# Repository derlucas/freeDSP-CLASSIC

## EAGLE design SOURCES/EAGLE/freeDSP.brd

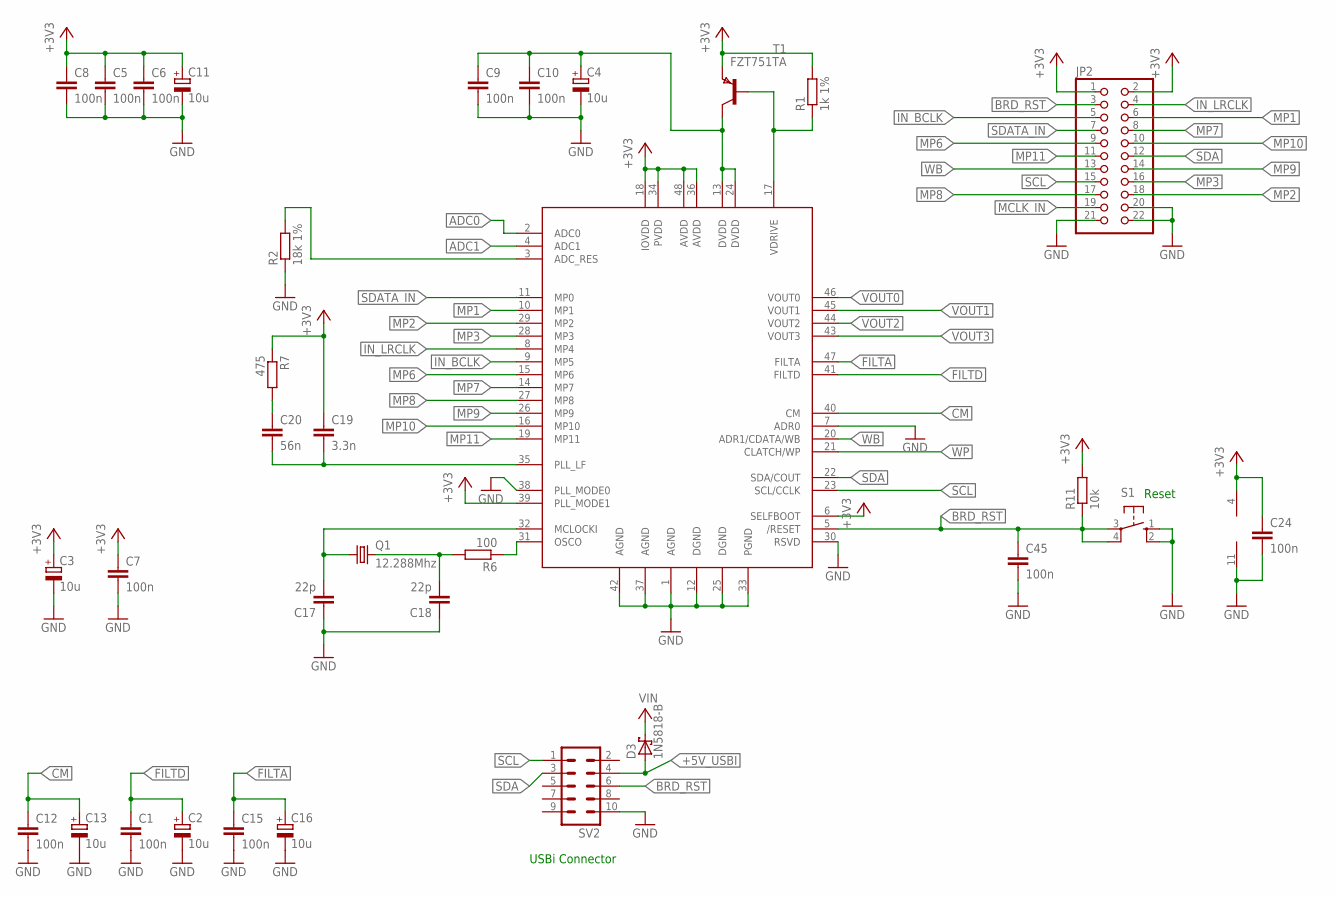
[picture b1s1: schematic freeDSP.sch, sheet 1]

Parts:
C1, C5, C6, C7, C8, C9, C10, C12, C15, C24, C45: 100n; C025-025X050
C2, C3, C4, C11, C13, C16: 10u; E1,8-4
C17, C18: 22p; C025-025X050
C19: 3.3n; C025-025X050
C20: 56n; C025-025X050
D3: 1N5818-B; DO41-7.6
IC3: AD8608R; SO-14
JP2: PINHD-2X11; 2X11
Q1: 12.288Mhz; HC49/S
R1: 1k 1%; 0207/10
R2: 18k 1%; 0207/10
R6: 100; 0207/10
R7: 475; 0207/10
R11: 10k; 0207/10
S1: 10-XX; B3F-10XX
SV2: ML10
T1: FZT751TA; SOT223
U$1: ADAU1701; LQFP-48

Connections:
1V8: C4.+, C9.1, C10.1, T1.2 (C), T1.4 (C), U$1.13 (DVDD), U$1.24 (DVDD)
+3V3: C3.+, C5.1, C6.1, C7.1, C8.1, C11.+, C19.1, C24.1, IC3.4 (V+), JP2.1, JP2.2, R1.2, R7.1, R11.2, T1.3 (E), U$1.6 (SELFBOOT), U$1.18 (IOVDD), U$1.34 (PVDD), U$1.36 (AVDD), U$1.39 (PLL_MODE1), U$1.48 (AVDD); also elsewhere on the board
+5V_USBI: D3.A, SV2.4
ADC0: U$1.2 (ADC0); also elsewhere on the board
ADC1: U$1.4 (ADC1); also elsewhere on the board
BRD_RST: C45.1, JP2.3, R11.1, S1.3, S1.4 (P1), SV2.6, U$1.5 (/RESET); also elsewhere on the board
CM: C12.1, C13.+, U$1.40 (CM)
FILTA: C15.1, C16.+, U$1.47 (FILTA)
FILTD: C1.1, C2.+, U$1.41 (FILTD)
GND: C1.2, C2.-, C3.-, C4.-, C5.2, C6.2, C7.2, C8.2, C9.2, C10.2, C11.-, C12.2, C13.-, C15.2, C16.-, C17.1, C18.1, C24.2, C45.2, IC3.11 (V-), JP2.20, JP2.21, JP2.22, R2.1, S1.1 (S), S1.2 (S1), SV2.10, U$1.1 (AGND), U$1.7 (ADR0), U$1.12 (DGND), U$1.25 (DGND), U$1.30 (RSVD), U$1.33 (PGND), U$1.37 (AGND), U$1.38 (PLL_MODE0), U$1.42 (AGND); also elsewhere on the board
IN_BCLK: JP2.5, U$1.9 (MP5)
IN_LRCLK: JP2.4, U$1.8 (MP4)
MCLK_IN: JP2.19
MP1: JP2.6, U$1.10 (MP1)
MP2: JP2.18, U$1.29 (MP2)
MP3: JP2.16, U$1.28 (MP3)
MP6: JP2.9, U$1.15 (MP6)
MP7: JP2.8, U$1.14 (MP7)
MP8: JP2.17, U$1.27 (MP8)
MP9: JP2.14, U$1.26 (MP9)
MP10: JP2.10, U$1.16 (MP10)
MP11: JP2.11, U$1.19 (MP11)
unnamed: R2.2, U$1.3 (ADC_RES)
unnamed: R1.1, T1.1 (B), U$1.17 (VDRIVE)
unnamed: C19.2, C20.2, U$1.35 (PLL_LF)
unnamed: C20.1, R7.2
unnamed: C18.2, Q1.2, R6.2
unnamed: R6.1, U$1.31 (OSCO)
unnamed: C17.2, Q1.1, U$1.32 (MCLOCKI)
SCL: JP2.15, SV2.1, U$1.23 (SCL/CCLK); also elsewhere on the board
SDA: JP2.12, SV2.3, U$1.22 (SDA/COUT); also elsewhere on the board
SDATA_IN: JP2.7, U$1.11 (MP0)
V+: D3.C; also elsewhere on the board
VOUT0: U$1.46 (VOUT0); also elsewhere on the board
VOUT1: U$1.45 (VOUT1); also elsewhere on the board
VOUT2: U$1.44 (VOUT2); also elsewhere on the board
VOUT3: U$1.43 (VOUT3); also elsewhere on the board
WB: JP2.13, U$1.20 (ADR1/CDATA/WB)
WP: U$1.21 (CLATCH/WP); also elsewhere on the board

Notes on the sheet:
Reset
USBi Connector

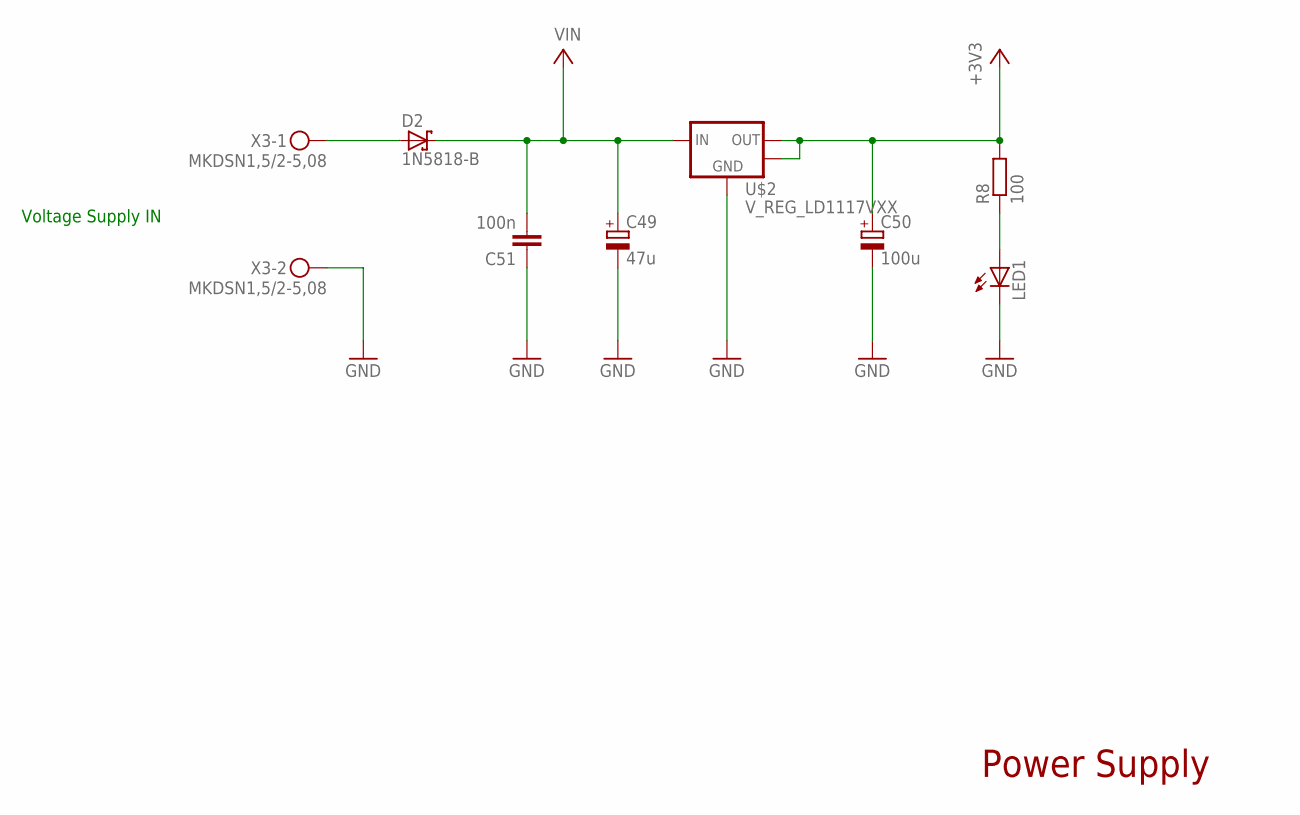
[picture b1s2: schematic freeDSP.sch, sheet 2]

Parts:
C49: 47u; E2,5-6
C50: 100u; E2,5-6
C51: 100n; C025-025X050
D2: 1N5818-B; DO41-7.6
LED1: LED3MM
R8: 100; 0207/10
U$2: V_REG_LD1117VXX; 78XXL
X3: MKDSN1,5/2-5,08

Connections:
+3V3: C50.+, R8.2, U$2.GND (OUT), U$2.OUT2; also elsewhere on the board
GND: C49.-, C50.-, C51.1, LED1.K (C), U$2.IN (GND), X3.2; also elsewhere on the board
unnamed: LED1.A, R8.1
unnamed: D2.A, X3.1
V+: C49.+, C51.2, D2.C, U$2.OUT (IN); also elsewhere on the board

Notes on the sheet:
Voltage Supply IN
Power Supply

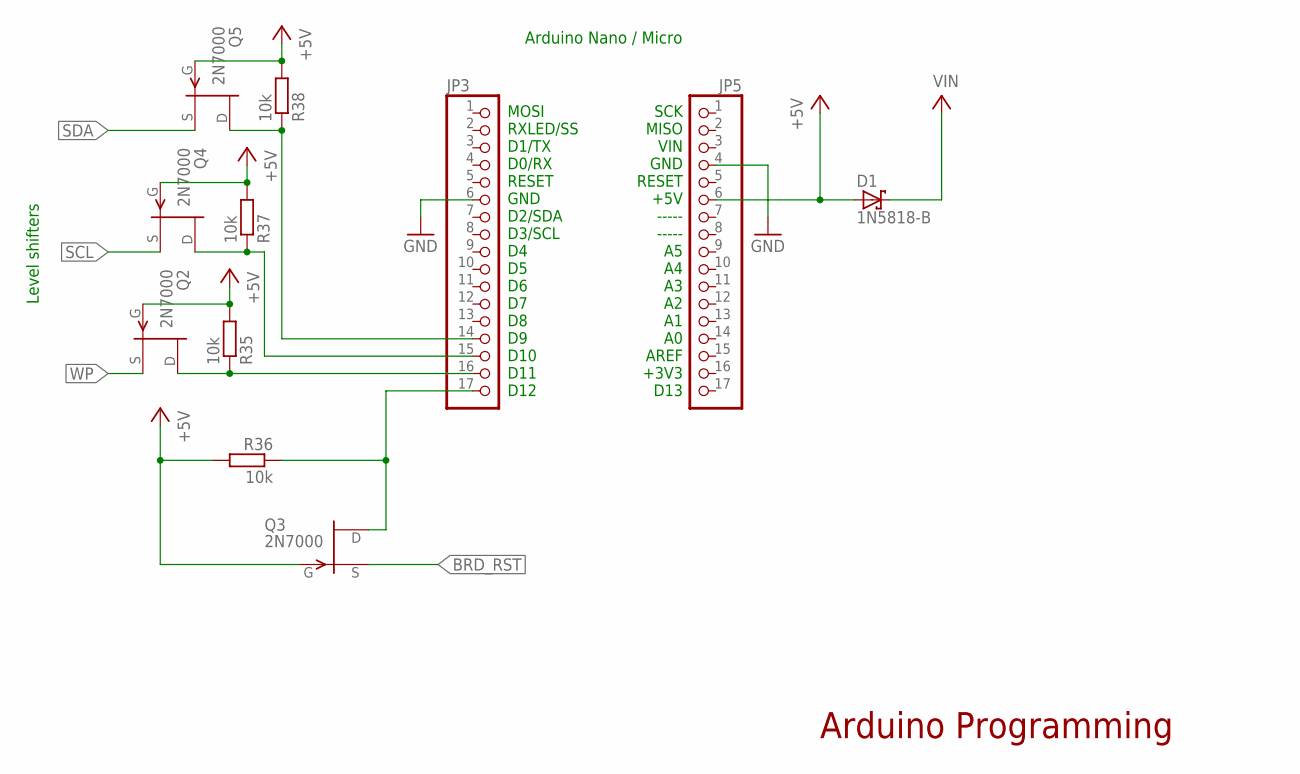
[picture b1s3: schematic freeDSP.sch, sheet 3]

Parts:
D1: 1N5818-B; DO41-7.6
JP3, JP5: PINHD-1X17; 1X17
Q2, Q3, Q4, Q5: 2N7000; TO92
R35, R36, R37, R38: 10k; 0207/10

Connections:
+5V: D1.A, JP5.6, Q2.2 (G), Q3.2 (G), Q4.2 (G), Q5.2 (G), R35.2, R36.2, R37.2, R38.2
BRD_RST: Q3.3 (S); also elsewhere on the board
GND: JP3.6, JP5.4; also elsewhere on the board
unnamed: JP3.15, Q4.1 (D), R37.1
unnamed: JP3.14, Q5.1 (D), R38.1
unnamed: JP3.16, Q2.1 (D), R35.1
unnamed: JP3.17, Q3.1 (D), R36.1
SCL: Q4.3 (S); also elsewhere on the board
SDA: Q5.3 (S); also elsewhere on the board
V+: D1.C; also elsewhere on the board
WP: Q2.3 (S); also elsewhere on the board

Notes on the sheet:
Arduino Programming
Arduino Nano / Micro
MOSI RXLED/SS D1/TX D0/RX RESET GND D2/SDA D3/SCL D4 D5 D6 D7 D8 D9 D10 D11 D12
SCK MISO VIN GND RESET +5V ----- ----- A5 A4 A3 A2 A1 A0 AREF +3V3 D13
Level shifters

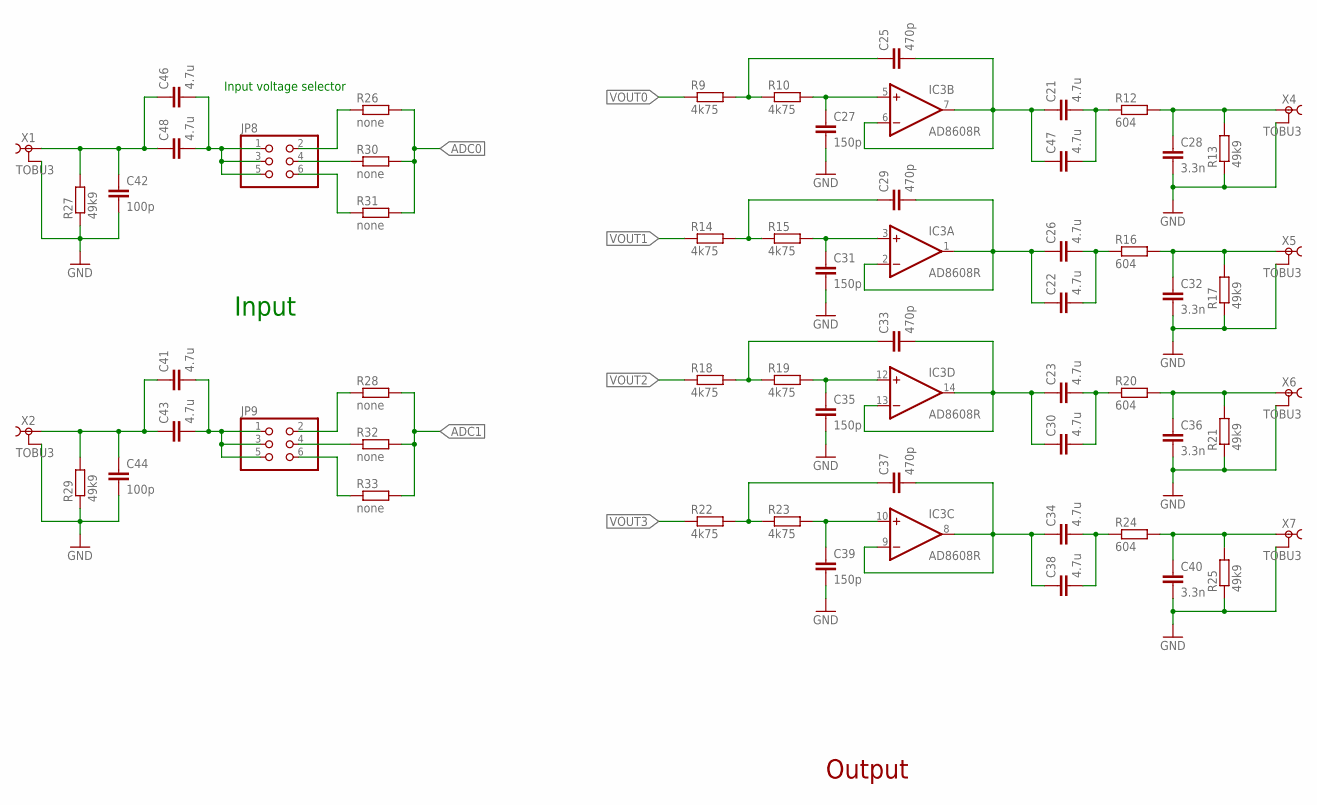
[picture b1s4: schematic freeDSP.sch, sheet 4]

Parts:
C21, C22, C23, C26, C30, C34, C38, C41, C43, C46, C47, C48: 4.7u; C050-075X075
C25, C29, C33, C37: 470p; C050-050X075
C27, C31, C35, C39: 150p; C025-025X050
C28, C32, C36, C40: 3.3n; C025-025X050
C42, C44: 100p; C025-025X050
IC3: AD8608R; SO-14
JP8, JP9: PINHD-2X3; 2X03
R9, R10, R14, R15, R18, R19, R22, R23: 4k75; 0207/10
R12, R16, R20, R24: 604; 0207/10
R13, R17, R21, R25, R27, R29: 49k9; 0207/10
R26, R28, R30, R31, R32, R33: none; 0207/10
X1, X2, X4, X5, X6, X7: TOBU3

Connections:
ADC0: R26.2, R30.2, R31.2; also elsewhere on the board
ADC1: R28.2, R32.2, R33.2; also elsewhere on the board
FILTOUT0: C28.1, R12.2, R13.2, X4.1
FILTOUT1: C32.1, R16.2, R17.2, X5.1
FILTOUT2: C36.1, R20.2, R21.2, X6.1
FILTOUT3: C40.1, R24.2, R25.2, X7.1
GND: C27.2, C28.2, C31.2, C32.2, C35.2, C36.2, C39.2, C40.2, C42.2, C44.2, R13.1, R17.1, R21.1, R25.1, R27.1, R29.1, X1.2, X1.2@1 (2), X1.2@2 (2), X2.2, X2.2@1 (2), X2.2@2 (2), X4.2, X4.2@1 (2), X4.2@2 (2), X5.2, X5.2@1 (2), X5.2@2 (2), X6.2, X6.2@1 (2), X6.2@2 (2), X7.2, X7.2@1 (2), X7.2@2 (2); also elsewhere on the board
unnamed: C23.1, C30.1, C33.2, IC3.13 (-IN), IC3.14 (OUT)
unnamed: C21.2, C47.2, R12.1
unnamed: C29.1, R14.2, R15.1
unnamed: C22.1, C26.1, C29.2, IC3.1 (OUT), IC3.2 (-IN)
unnamed: C31.1, IC3.3 (+IN), R15.2
unnamed: C25.1, R9.2, R10.1
unnamed: C21.1, C25.2, C47.1, IC3.6 (-IN), IC3.7 (OUT)
unnamed: C22.2, C26.2, R16.1
unnamed: C27.1, IC3.5 (+IN), R10.2
unnamed: C33.1, R18.2, R19.1
unnamed: C23.2, C30.2, R20.1
unnamed: C35.1, IC3.12 (+IN), R19.2
unnamed: C37.1, R22.2, R23.1
unnamed: C34.1, C37.2, C38.1, IC3.8 (OUT), IC3.9 (-IN)
unnamed: C39.1, IC3.10 (+IN), R23.2
unnamed: C34.2, C38.2, R24.1
unnamed: C46.2, C48.2, JP8.1, JP8.3, JP8.5
unnamed: C42.1, C46.1, C48.1, R27.2, X1.1
unnamed: JP8.2, R26.1
unnamed: JP8.4, R30.1
unnamed: C41.1, C43.1, C44.1, R29.2, X2.1
unnamed: JP8.6, R31.1
unnamed: C41.2, C43.2, JP9.1, JP9.3, JP9.5
unnamed: JP9.2, R28.1
unnamed: JP9.4, R32.1
unnamed: JP9.6, R33.1
VOUT0: R9.1; also elsewhere on the board
VOUT1: R14.1; also elsewhere on the board
VOUT2: R18.1; also elsewhere on the board
VOUT3: R22.1; also elsewhere on the board

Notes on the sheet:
Output
Input
Input voltage selector

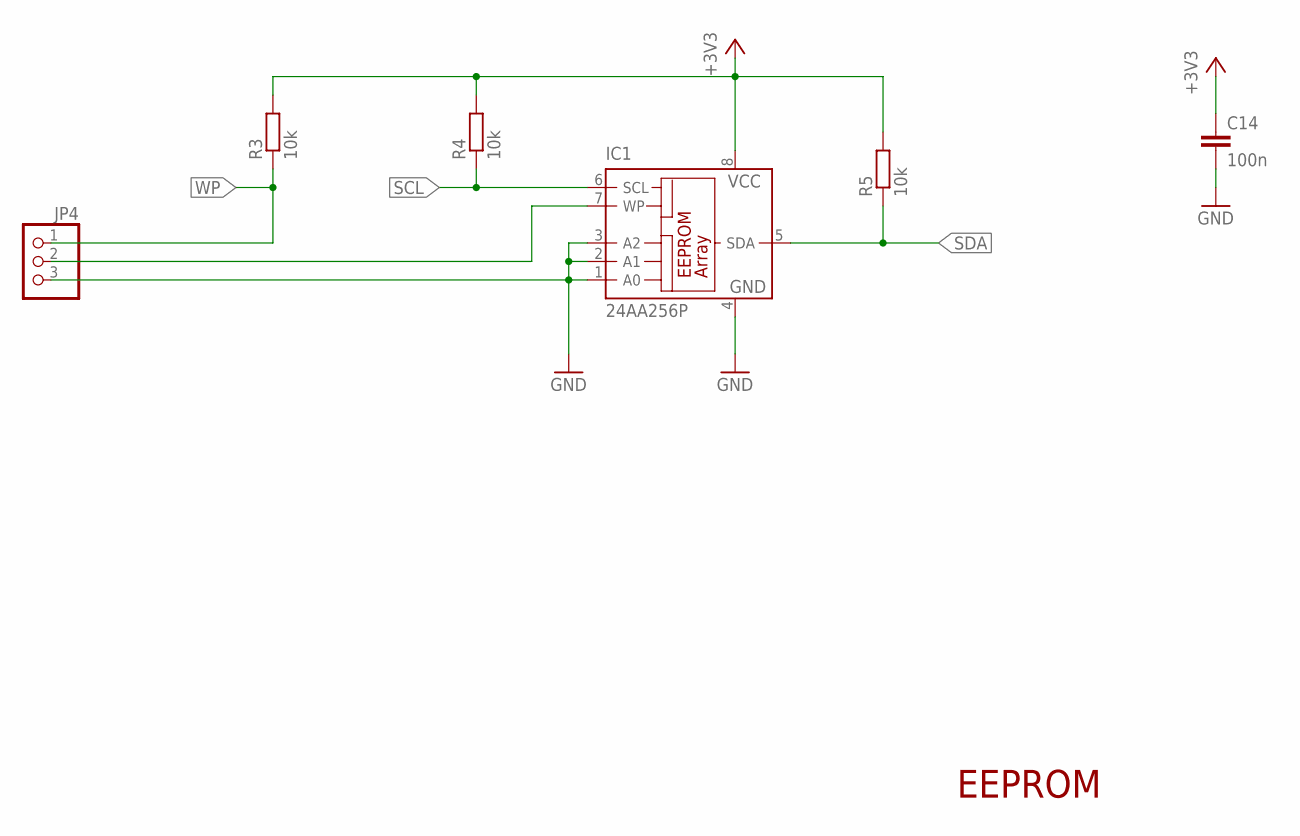
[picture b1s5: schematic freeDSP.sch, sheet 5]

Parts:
C14: 100n; C025-025X050
IC1: 24AA256P; DIL8
JP4: PINHD-1X3; 1X03
R3, R4, R5: 10k; 0207/10

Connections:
+3V3: C14.1, IC1.8 (VCC), R3.2, R4.2, R5.2; also elsewhere on the board
GND: C14.2, IC1.1 (A0), IC1.2 (A1), IC1.3 (A2), IC1.4 (GND), JP4.3; also elsewhere on the board
unnamed: IC1.7 (WP), JP4.2
SCL: IC1.6 (SCL), R4.1; also elsewhere on the board
SDA: IC1.5 (SDA), R5.1; also elsewhere on the board
WP: JP4.1, R3.1; also elsewhere on the board

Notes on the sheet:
EEPROM

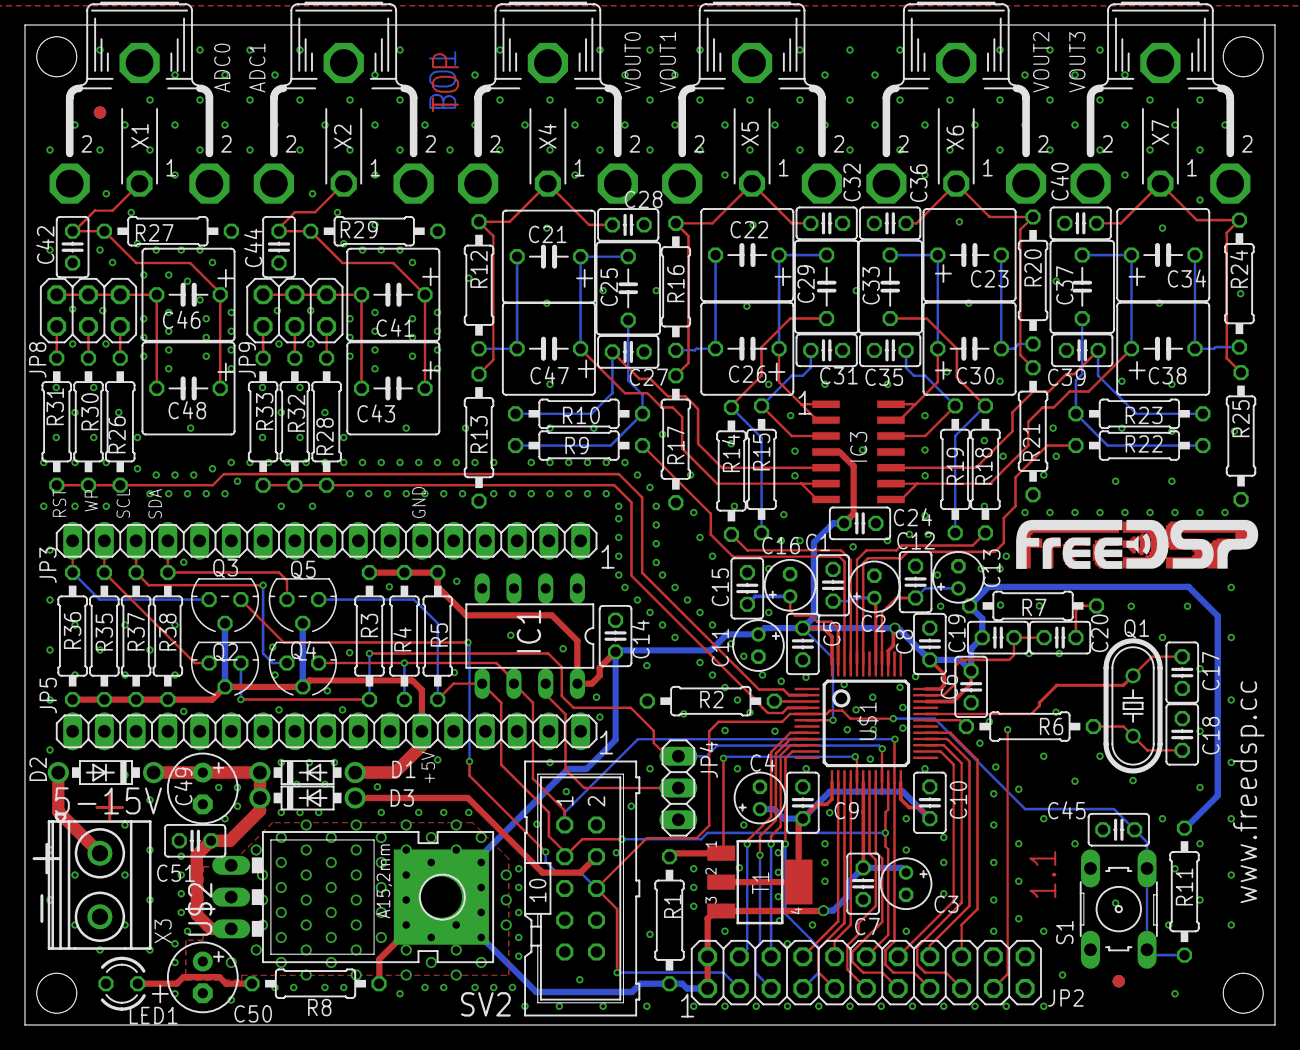
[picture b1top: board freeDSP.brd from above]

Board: 2 copper layers, 100.0 x 80.0 mm, 119 parts (0 on the bottom side), 76 nets.

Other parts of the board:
U$3, U$4: VISION_REF10

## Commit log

2016-01-29 cleaned up the schematic and moved parts to different sheets
2016-01-29 cleaned up sheet 0 and edited ADAU1701 to be smaller in the schematic

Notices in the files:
parts and their libraries:
SparkFun-PowerIC: Licensing: Creative Commons ShareAlike 4.0 International - https://creativecommons.org/licenses/by-sa/4.0
dicons: Copyright (C) 2004, Bob Starr (rtzaudio@mindspring.com)
